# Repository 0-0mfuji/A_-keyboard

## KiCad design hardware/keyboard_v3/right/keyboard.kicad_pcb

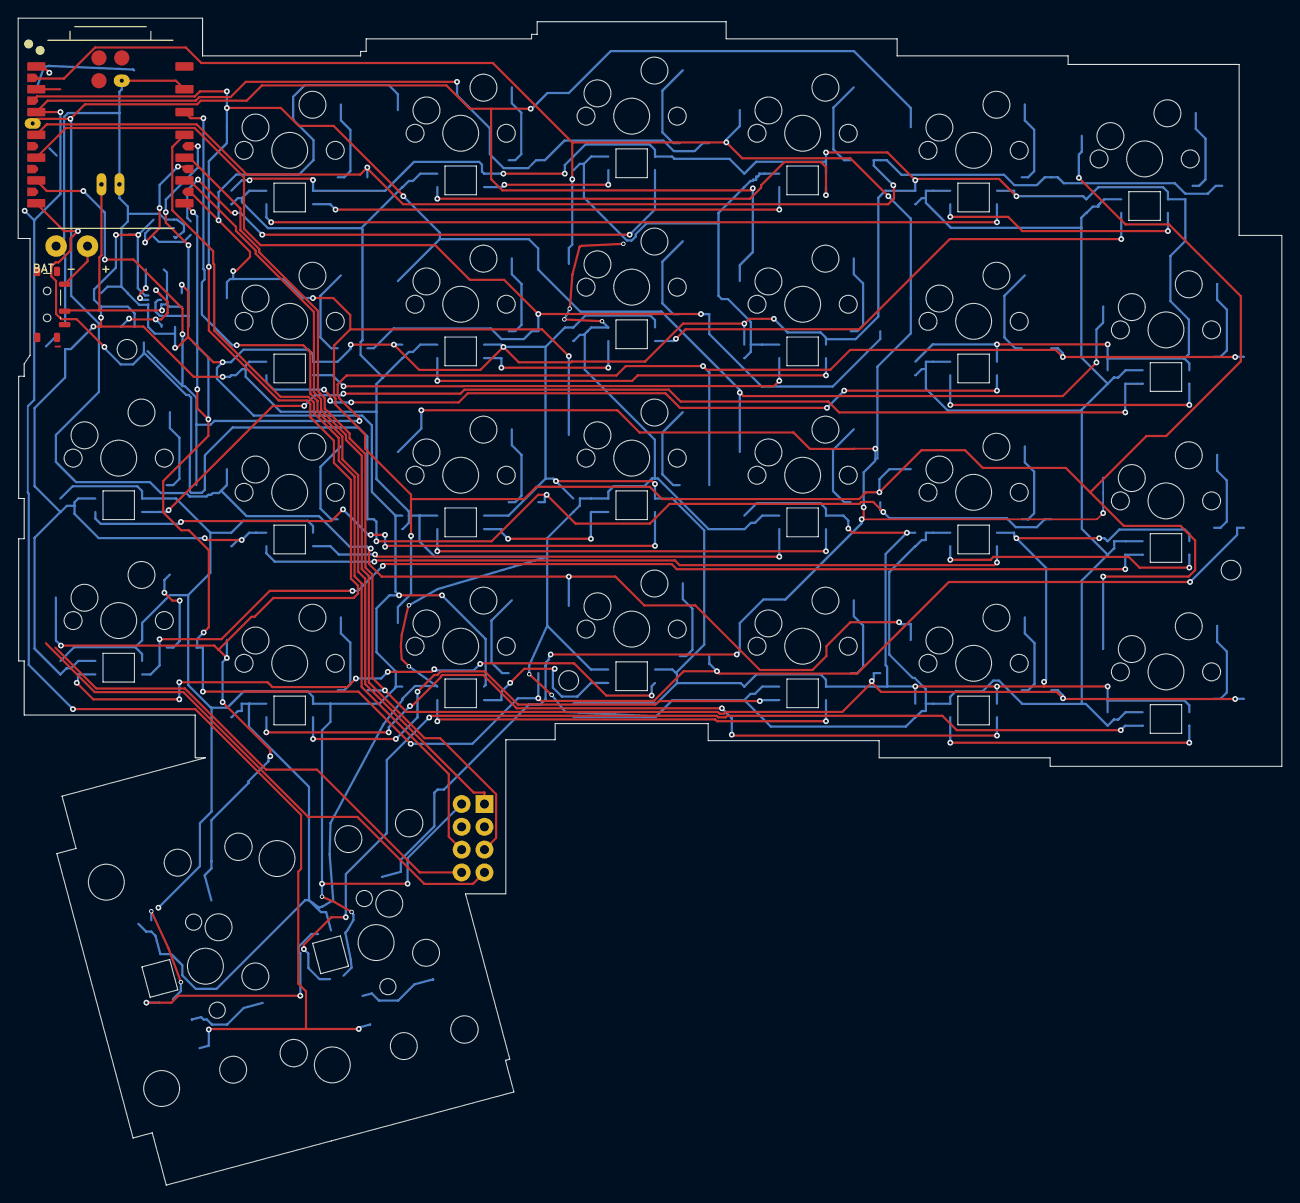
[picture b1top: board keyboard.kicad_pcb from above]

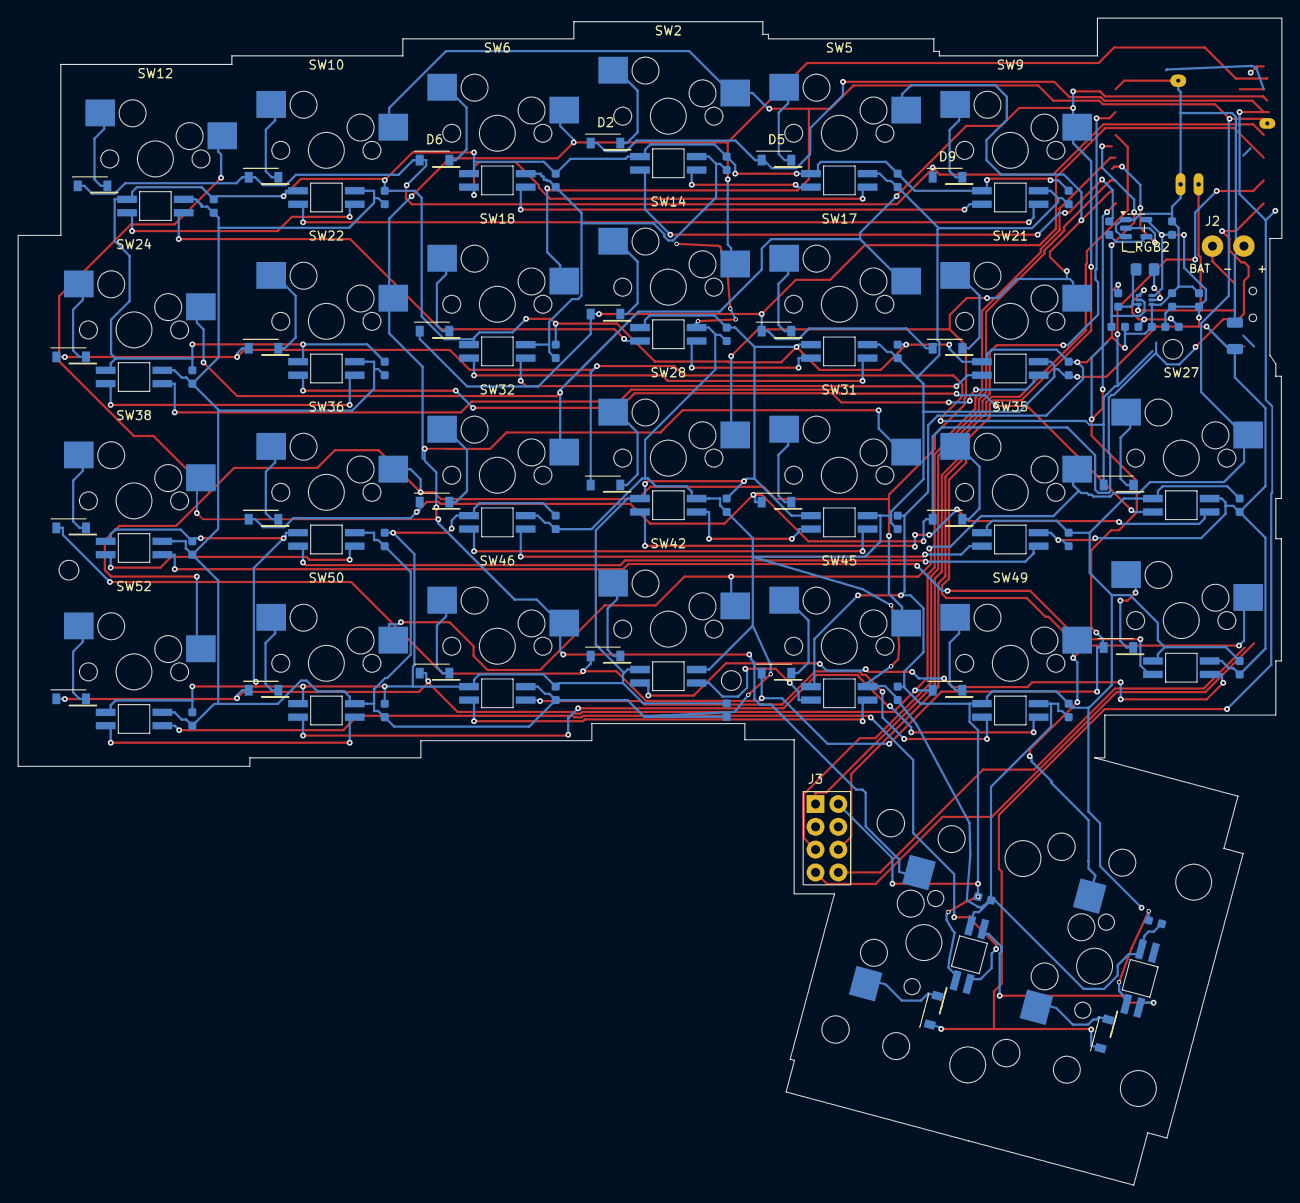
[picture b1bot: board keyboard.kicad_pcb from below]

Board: 2 copper layers, 140.8 x 130.0 mm, 135 parts (98 on the bottom side), 81 nets.

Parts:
C_LS2: 100nF; C_0603
C_RGB2, C_RGB5, C_RGB6, C_RGB9, C_RGB10, C_RGB12, C_RGB14, C_RGB17, C_RGB18, C_RGB21, C_RGB22, C_RGB24, C_RGB27, C_RGB28, C_RGB31, C_RGB32, C_RGB35, C_RGB36, C_RGB38, C_RGB39, C_RGB42, C_RGB45, C_RGB46, C_RGB49, C_RGB50, C_RGB52, C_RGB56, C_RGB57: 100nF; C_0603
C_RGB_BULK2: 100uF; C_1206_3216Metric
C_RGB_IN2: 10uF; C_0603
C_RGB_OUT1_2, C_RGB_OUT2_2: 22uF; C_0603
D2, D5, D6, D9, D10, D12, D14, D17, D18, D21, D22, D24, D27, D28, D31, D32, D35, D36, D38, D39, D42, D45, D46, D49, D50, D52, D56, D57: 1N4148W; SOD123
H1, H2, H3: M2 NPTH clearance; MountingHole
J2: BAT wire pads (+/-); Battery_Wire_Pads
J3: SEIBOKU / jumper wires; SEIBOKU_JUMPER_HEADER
LED2, LED5, LED6, LED9, LED10, LED12, LED14, LED17, LED18, LED21, LED22, LED24, LED27, LED28, LED31, LED32, LED35, LED36, LED38, LED39, LED42, LED45, LED46, LED49, LED50, LED52, LED56, LED57: SK6812MINI-E; LED_SK6812MINI-E_BL
L_RGB2: 1uH; L_1008
R_RGB_DATA2: 220R; R_0603
R_RGB_EN_PD2: 100k; R_0603
R_RGB_FB_BOT2: 100k; R_0603
R_RGB_FB_TOP2: 732k; R_0603
STAB1, STAB2, STAB3, STAB4: MX stabilizer NPTH; MXStabilizerHole
SW2, SW5, SW6, SW9, SW10, SW12, SW14, SW17, SW18, SW21, SW22, SW27, SW28, SW31, SW32, SW35, SW36, SW39, SW42, SW45, SW46, SW49, SW50: MX; MX_Hotswap_1u
SW24, SW38, SW52: MX; MX_Hotswap_1.25u
SW56: MX; MX_Hotswap_2u
SW57: MX; MX_Hotswap_2.25u
SWP2: MSK-12C02 slide switch; PowerSwitch_MSK12C02
U2: XIAO nRF52840 Plus (SMD); XIAO_NRF52840_PLUS
U_LS2: SN74AHCT1G125
U_RGB2: TPS61023

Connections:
+3V3_RIGHT: J3.1, U2.12
/COL4: SW6.1, SW14.1, SW22.1, SW31.1, SW38.1, SW46.1, SW56.1, U2.15
/COL5: SW9.1, SW17.1, SW24.1, SW32.1, SW39.1, SW49.1, SW57.1, U2.16
/COL6: SW2.1, SW10.1, SW18.1, SW27.1, SW35.1, SW42.1, SW50.1, U2.17
/COL7: SW5.1, SW12.1, SW21.1, SW28.1, SW36.1, SW45.1, SW52.1, U2.21
/GND_RIGHT: C_LS2.2, C_RGB2.2, C_RGB5.2, C_RGB6.2, C_RGB9.2, C_RGB10.2, C_RGB12.2, C_RGB14.2, C_RGB17.2, C_RGB18.2, C_RGB21.2, C_RGB22.2, C_RGB24.2, C_RGB27.2, C_RGB28.2, C_RGB31.2, C_RGB32.2, C_RGB35.2, C_RGB36.2, C_RGB38.2, C_RGB39.2, C_RGB42.2, C_RGB45.2, C_RGB46.2, C_RGB49.2, C_RGB50.2, C_RGB52.2, C_RGB56.2, C_RGB57.2, C_RGB_BULK2.2, C_RGB_IN2.2, C_RGB_OUT1_2.2, C_RGB_OUT2_2.2, J2.2, J3.2, LED2.2, LED5.2, LED6.2, LED9.2, LED10.2, LED12.2, LED14.2, LED17.2, LED18.2, LED21.2, LED22.2, LED24.2, LED27.2, LED28.2, LED31.2, LED32.2, LED35.2, LED36.2, LED38.2, LED39.2, LED42.2, LED45.2, LED46.2, LED49.2, LED50.2, LED52.2, LED56.2, LED57.2, R_RGB_EN_PD2.2, R_RGB_FB_BOT2.2, U2.13, U2.27, U2.29, U_LS2.1, U_LS2.3, U_RGB2.4
/RGB_5V_RIGHT: C_LS2.1, C_RGB2.1, C_RGB5.1, C_RGB6.1, C_RGB9.1, C_RGB10.1, C_RGB12.1, C_RGB14.1, C_RGB17.1, C_RGB18.1, C_RGB21.1, C_RGB22.1, C_RGB24.1, C_RGB27.1, C_RGB28.1, C_RGB31.1, C_RGB32.1, C_RGB35.1, C_RGB36.1, C_RGB38.1, C_RGB39.1, C_RGB42.1, C_RGB45.1, C_RGB46.1, C_RGB49.1, C_RGB50.1, C_RGB52.1, C_RGB56.1, C_RGB57.1, C_RGB_BULK2.1, C_RGB_OUT1_2.1, C_RGB_OUT2_2.1, LED2.1, LED5.1, LED6.1, LED9.1, LED10.1, LED12.1, LED14.1, LED17.1, LED18.1, LED21.1, LED22.1, LED24.1, LED27.1, LED28.1, LED31.1, LED32.1, LED35.1, LED36.1, LED38.1, LED39.1, LED42.1, LED45.1, LED46.1, LED49.1, LED50.1, LED52.1, LED56.1, LED57.1, R_RGB_FB_TOP2.1, U_LS2.5, U_RGB2.6
/RGB_DATA_RIGHT: U2.22, U_LS2.2
/RGB_DATA_SHIFTED_RIGHT: LED2.3, R_RGB_DATA2.2
/RGB_EN_RIGHT: R_RGB_EN_PD2.1, U2.23, U_RGB2.2
/ROW8: D2.1, D5.1, D56.1, D57.1, U2.3
/ROW9: D6.1, D9.1, D10.1, D12.1, U2.4
/ROW10: D14.1, D17.1, D18.1, D21.1, U2.5
/ROW11: D22.1, D24.1, D27.1, D28.1, U2.6
/ROW12: D31.1, D32.1, D35.1, D36.1, U2.7
/ROW13: D38.1, D39.1, D42.1, D45.1, U2.8
/ROW14: D46.1, D49.1, D50.1, D52.1, U2.10
/VBAT_RIGHT: C_RGB_IN2.1, L_RGB2.1, SWP2.2, U2.28, U_RGB2.3
/controller/pmw3610_0_MOTION: J3.7, U2.1
/controller/pmw3610_0_NCS: J3.8, U2.2
/controller/pmw3610_0_SCLK: J3.5, U2.9
/controller/pmw3610_0_SDIO: J3.6, U2.11
/matrix/SW2_A: D2.2, SW2.2
/matrix/SW5_A: D5.2, SW5.2
/matrix/SW6_A: D6.2, SW6.2
/matrix/SW9_A: D9.2, SW9.2
/matrix/SW10_A: D10.2, SW10.2
/matrix/SW12_A: D12.2, SW12.2
/matrix/SW14_A: D14.2, SW14.2
/matrix/SW17_A: D17.2, SW17.2
/matrix/SW18_A: D18.2, SW18.2
/matrix/SW21_A: D21.2, SW21.2
/matrix/SW22_A: D22.2, SW22.2
/matrix/SW24_A: D24.2, SW24.2
/matrix/SW27_A: D27.2, SW27.2
/matrix/SW28_A: D28.2, SW28.2
/matrix/SW31_A: D31.2, SW31.2
/matrix/SW32_A: D32.2, SW32.2
/matrix/SW35_A: D35.2, SW35.2
/matrix/SW36_A: D36.2, SW36.2
/matrix/SW38_A: D38.2, SW38.2
/matrix/SW39_A: D39.2, SW39.2
/matrix/SW42_A: D42.2, SW42.2
/matrix/SW45_A: D45.2, SW45.2
/matrix/SW46_A: D46.2, SW46.2
/matrix/SW49_A: D49.2, SW49.2
/matrix/SW50_A: D50.2, SW50.2
/matrix/SW52_A: D52.2, SW52.2
/matrix/SW56_A: D56.2, SW56.2
/matrix/SW57_A: D57.2, SW57.2
/power/BAT_RAW_RIGHT: J2.1, SWP2.1
/power/RGB_FB_RIGHT: R_RGB_FB_BOT2.1, R_RGB_FB_TOP2.2, U_RGB2.1
/power/RGB_SHIFTED_RIGHT: R_RGB_DATA2.1, U_LS2.4
/power/RGB_SW_RIGHT: L_RGB2.2, U_RGB2.5
/rgb/RGB_LED_right_0: LED2.4, LED5.3
/rgb/RGB_LED_right_1: LED5.4, LED6.3
/rgb/RGB_LED_right_2: LED6.4, LED9.3
/rgb/RGB_LED_right_3: LED9.4, LED10.3
/rgb/RGB_LED_right_4: LED10.4, LED12.3
/rgb/RGB_LED_right_5: LED12.4, LED14.3
/rgb/RGB_LED_right_6: LED14.4, LED17.3
/rgb/RGB_LED_right_7: LED17.4, LED18.3
/rgb/RGB_LED_right_8: LED18.4, LED21.3
/rgb/RGB_LED_right_9: LED21.4, LED22.3
/rgb/RGB_LED_right_10: LED22.4, LED24.3
/rgb/RGB_LED_right_11: LED24.4, LED27.3
/rgb/RGB_LED_right_12: LED27.4, LED28.3
/rgb/RGB_LED_right_13: LED28.4, LED31.3
/rgb/RGB_LED_right_14: LED31.4, LED32.3
/rgb/RGB_LED_right_15: LED32.4, LED35.3
/rgb/RGB_LED_right_16: LED35.4, LED36.3
/rgb/RGB_LED_right_17: LED36.4, LED38.3
/rgb/RGB_LED_right_18: LED38.4, LED39.3
/rgb/RGB_LED_right_19: LED39.4, LED42.3
/rgb/RGB_LED_right_20: LED42.4, LED45.3
/rgb/RGB_LED_right_21: LED45.4, LED46.3
/rgb/RGB_LED_right_22: LED46.4, LED49.3
/rgb/RGB_LED_right_23: LED49.4, LED50.3
/rgb/RGB_LED_right_24: LED50.4, LED52.3
/rgb/RGB_LED_right_25: LED52.4, LED56.3
/rgb/RGB_LED_right_26: LED56.4, LED57.3
